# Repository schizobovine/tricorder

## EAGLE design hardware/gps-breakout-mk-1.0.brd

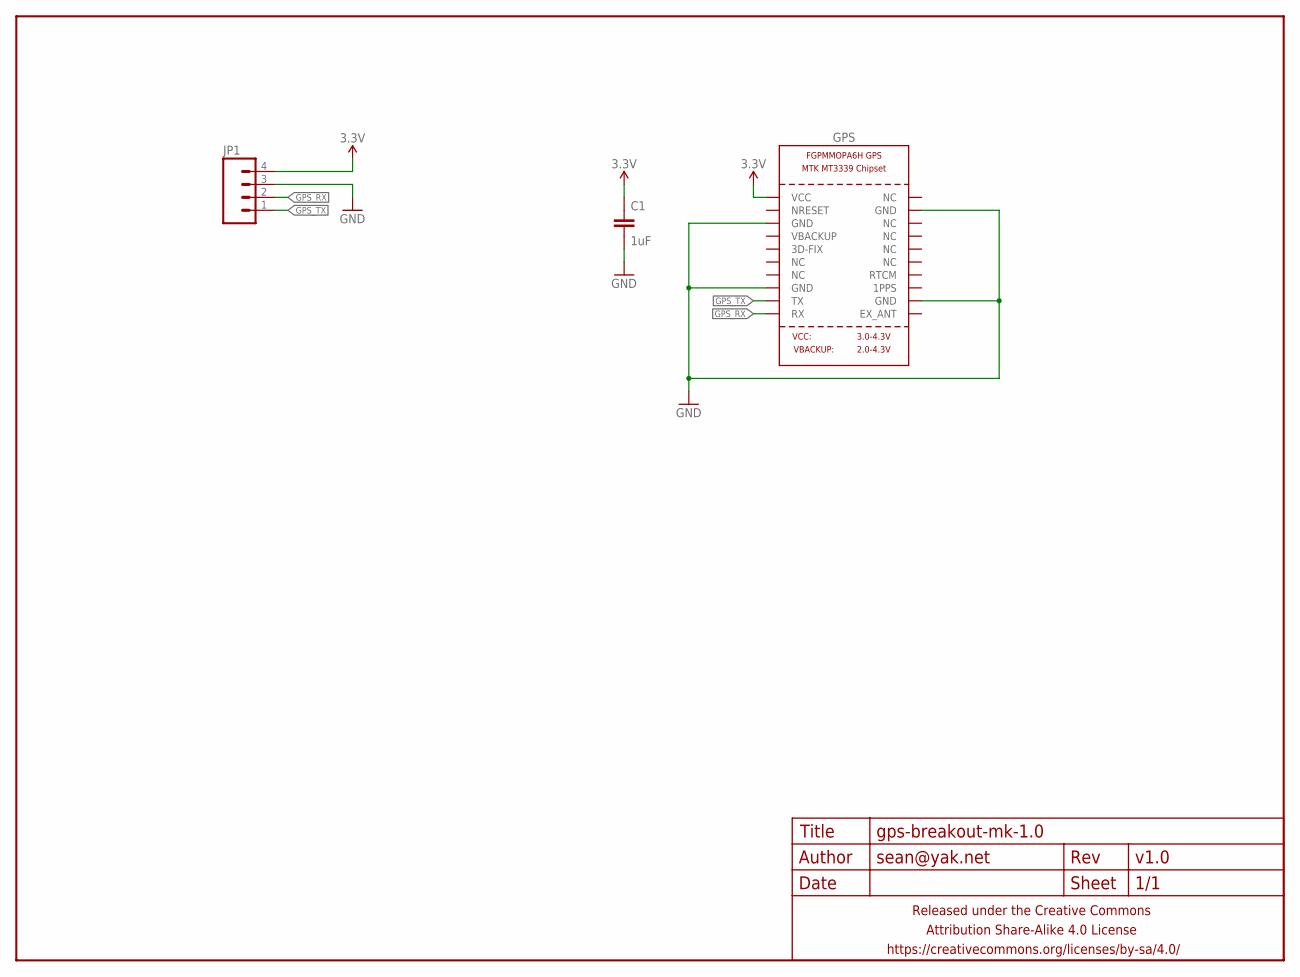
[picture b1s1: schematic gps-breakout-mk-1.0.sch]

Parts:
C1: 1uF; C0603
FRAME1: FRAME-LETTERNO_PACKAGE; DUMMY
GPS: GPS_FGPMMOPA6H; FGPMMOPA6H
JP1: M04PTH-NS-CENTERED; 1X04-PTH-VERT-NS-CENTERED

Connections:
3.3V: C1.1, GPS.P$1 (VCC), JP1.4
GND: C1.2, GPS.P$3 (GND), GPS.P$8 (GND), GPS.P$12 (GND), GPS.P$19 (GND), JP1.3
GPS_RX: GPS.P$10 (RX), JP1.2
GPS_TX: GPS.P$9 (TX), JP1.1

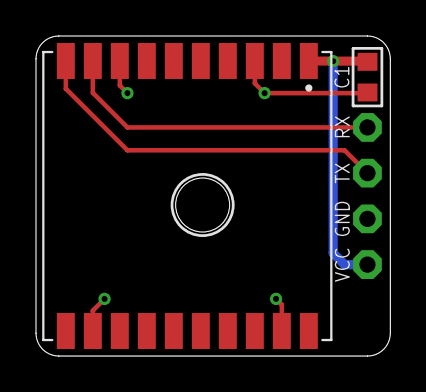
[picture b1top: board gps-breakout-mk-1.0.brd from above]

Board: 2 copper layers, 19.7 x 17.8 mm, 4 parts (0 on the bottom side), 4 nets.

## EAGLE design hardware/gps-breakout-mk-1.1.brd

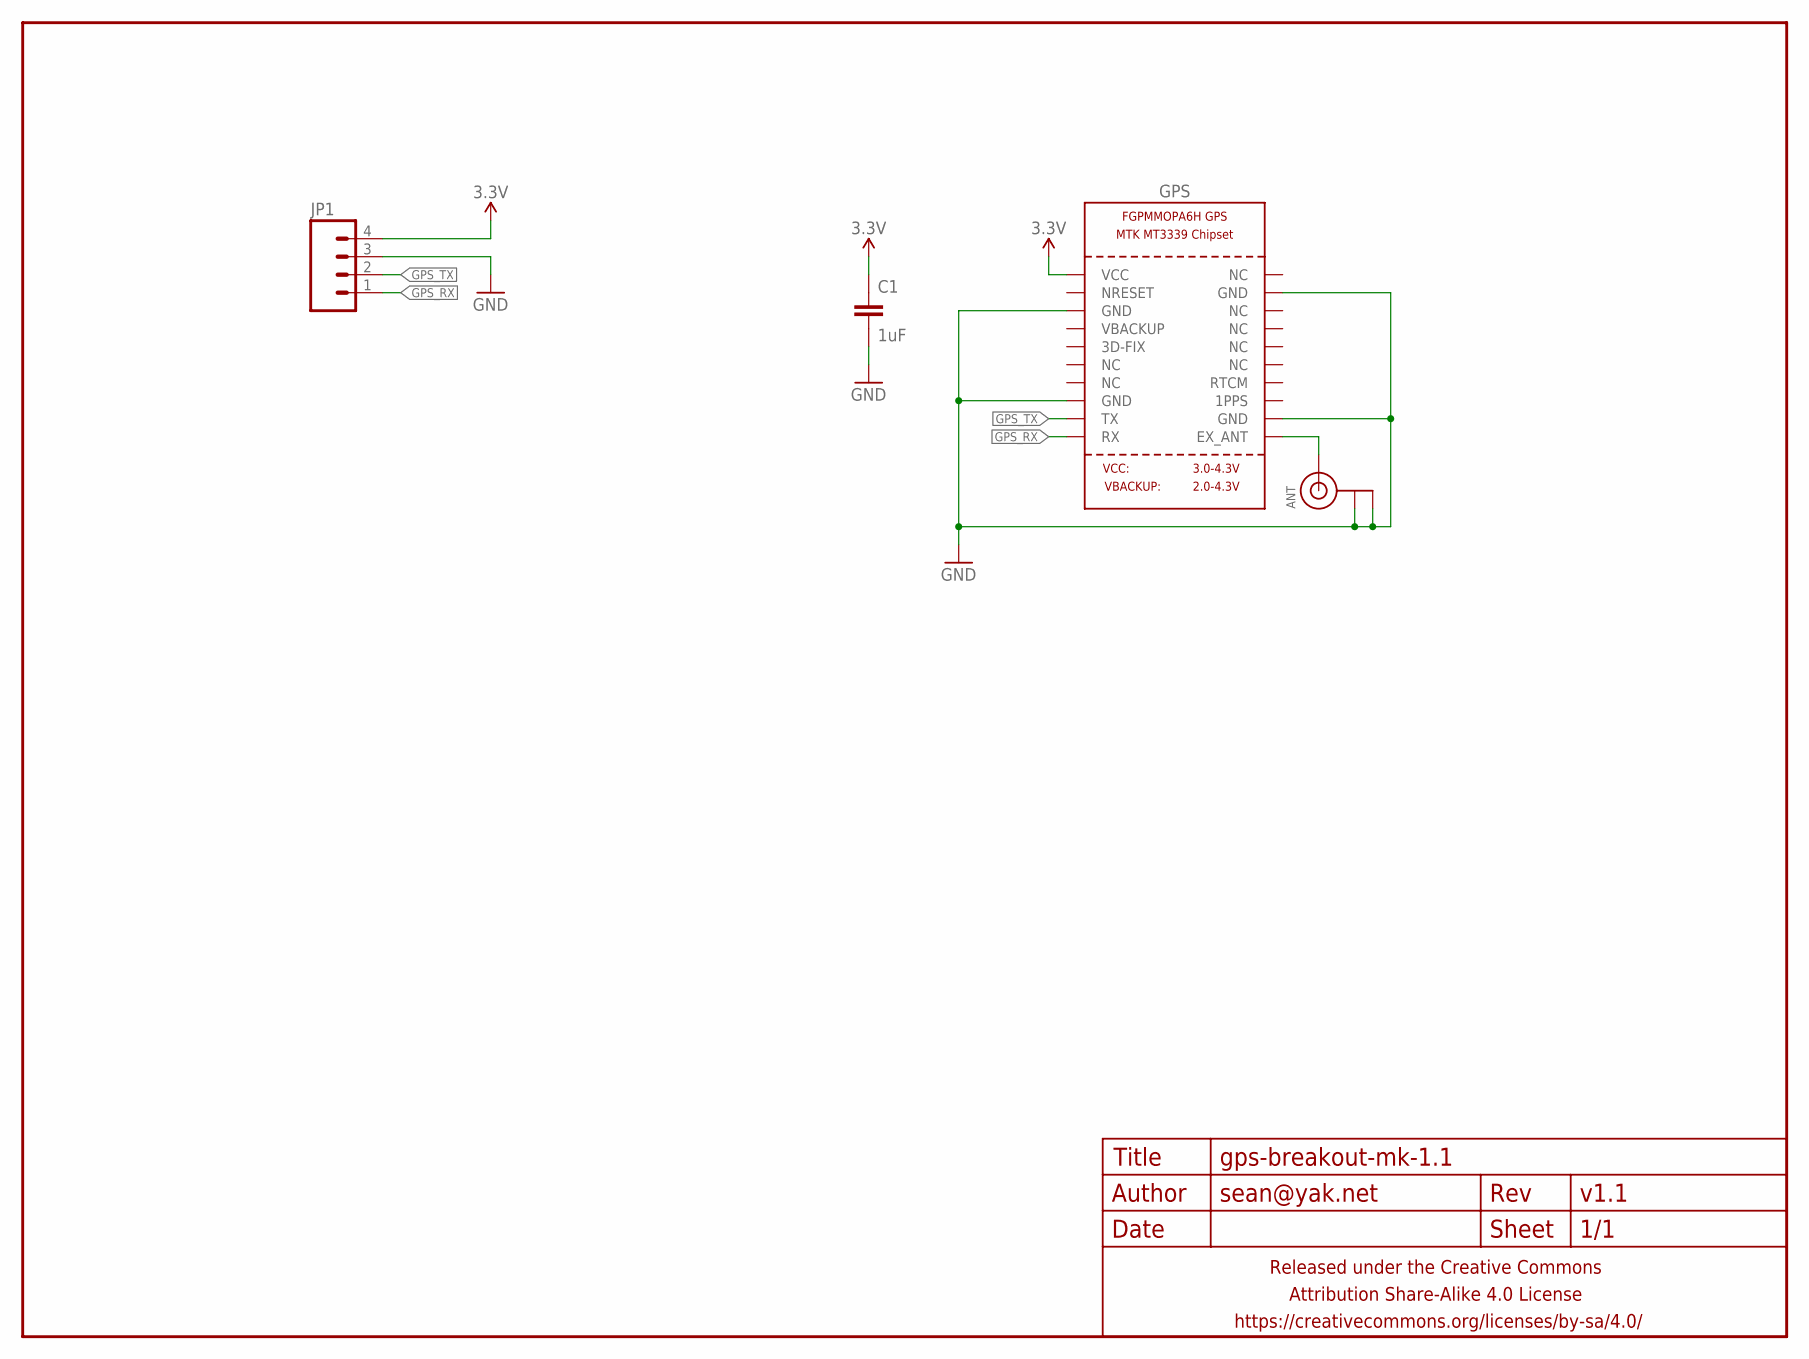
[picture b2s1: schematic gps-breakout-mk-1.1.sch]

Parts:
ANT: ANTENNA_U.FL; U.FL
C1: 1uF; C0402
FRAME1: FRAME-LETTERNO_PACKAGE; DUMMY
GPS: GPS_FGPMMOPA6H; FGPMMOPA6H
JP1: M04PTH-NS-CENTERED; 1X04-PTH-VERT-NS-CENTERED

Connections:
3.3V: C1.1, GPS.P$1 (VCC), JP1.4
GND: ANT.1 (GND), ANT.2 (GND), C1.2, GPS.P$3 (GND), GPS.P$8 (GND), GPS.P$12 (GND), GPS.P$19 (GND), JP1.3
GPS_RX: GPS.P$10 (RX), JP1.1
GPS_TX: GPS.P$9 (TX), JP1.2
unnamed: ANT.3 (SIGNAL), GPS.P$11 (EX_ANT)

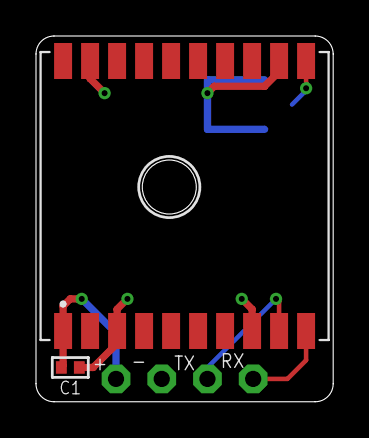
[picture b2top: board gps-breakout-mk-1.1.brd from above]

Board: 2 copper layers, 16.5 x 20.3 mm, 5 parts (1 on the bottom side), 5 nets.

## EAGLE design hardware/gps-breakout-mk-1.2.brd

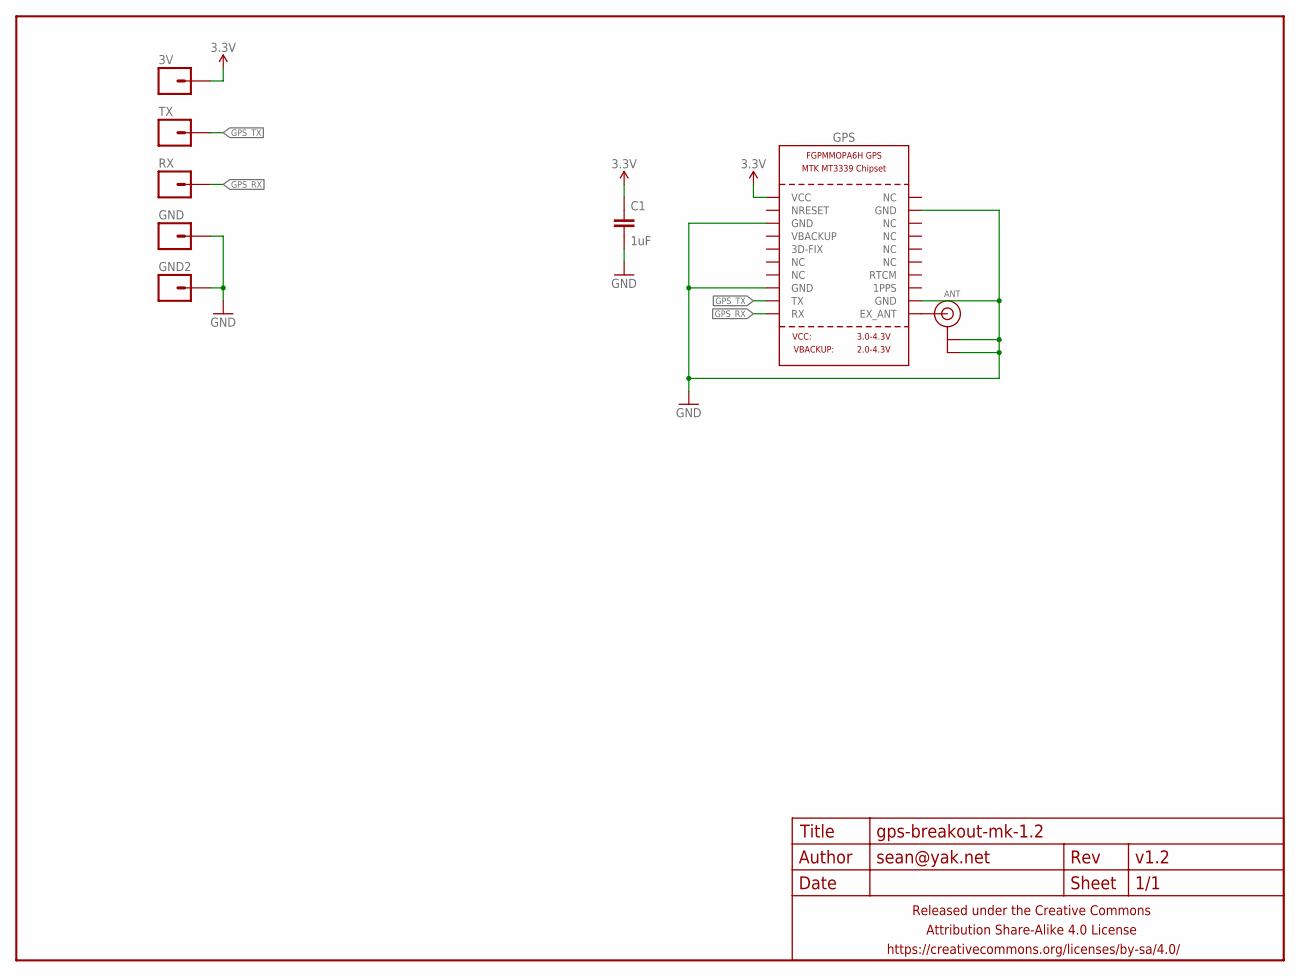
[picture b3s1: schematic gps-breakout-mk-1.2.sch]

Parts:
3V: M01PTH-1MM; 1X01-1MM-NS
ANT: ANTENNA_U.FL; U.FL
C1: 1uF; C0603-TIGHTER
FRAME1: FRAME-LETTERNO_PACKAGE; DUMMY
GND, GND2: M01PTH-1MM; 1X01-1MM-NS
GPS: GPS_FGPMMOPA6H; FGPMMOPA6H
RX: M01PTH-1MM; 1X01-1MM-NS
TX: M01PTH-1MM; 1X01-1MM-NS

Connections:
3.3V: 3V.1, C1.1, GPS.P$1 (VCC)
GND: ANT.1 (GND), ANT.2 (GND), C1.2, GND.1, GND2.1, GPS.P$3 (GND), GPS.P$8 (GND), GPS.P$12 (GND), GPS.P$19 (GND)
GPS_RX: GPS.P$10 (RX), RX.1
GPS_TX: GPS.P$9 (TX), TX.1
unnamed: ANT.3 (SIGNAL), GPS.P$11 (EX_ANT)

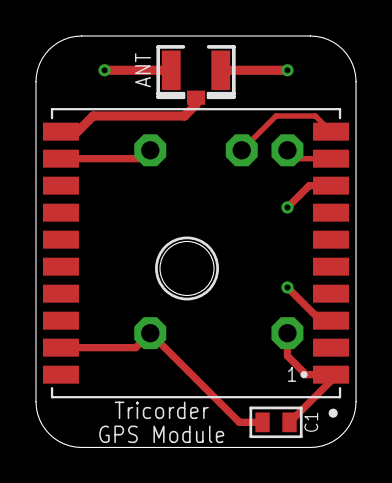
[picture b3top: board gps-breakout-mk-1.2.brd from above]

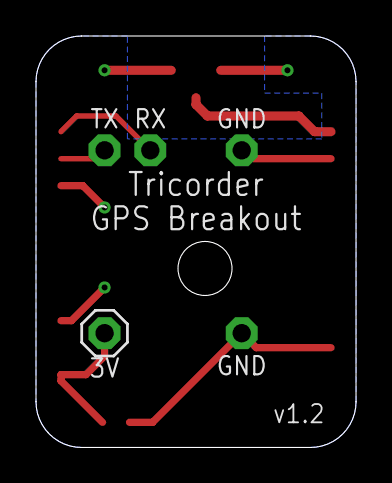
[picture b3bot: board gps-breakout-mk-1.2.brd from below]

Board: 2 copper layers, 17.8 x 22.9 mm, 9 parts (5 on the bottom side), 5 nets.

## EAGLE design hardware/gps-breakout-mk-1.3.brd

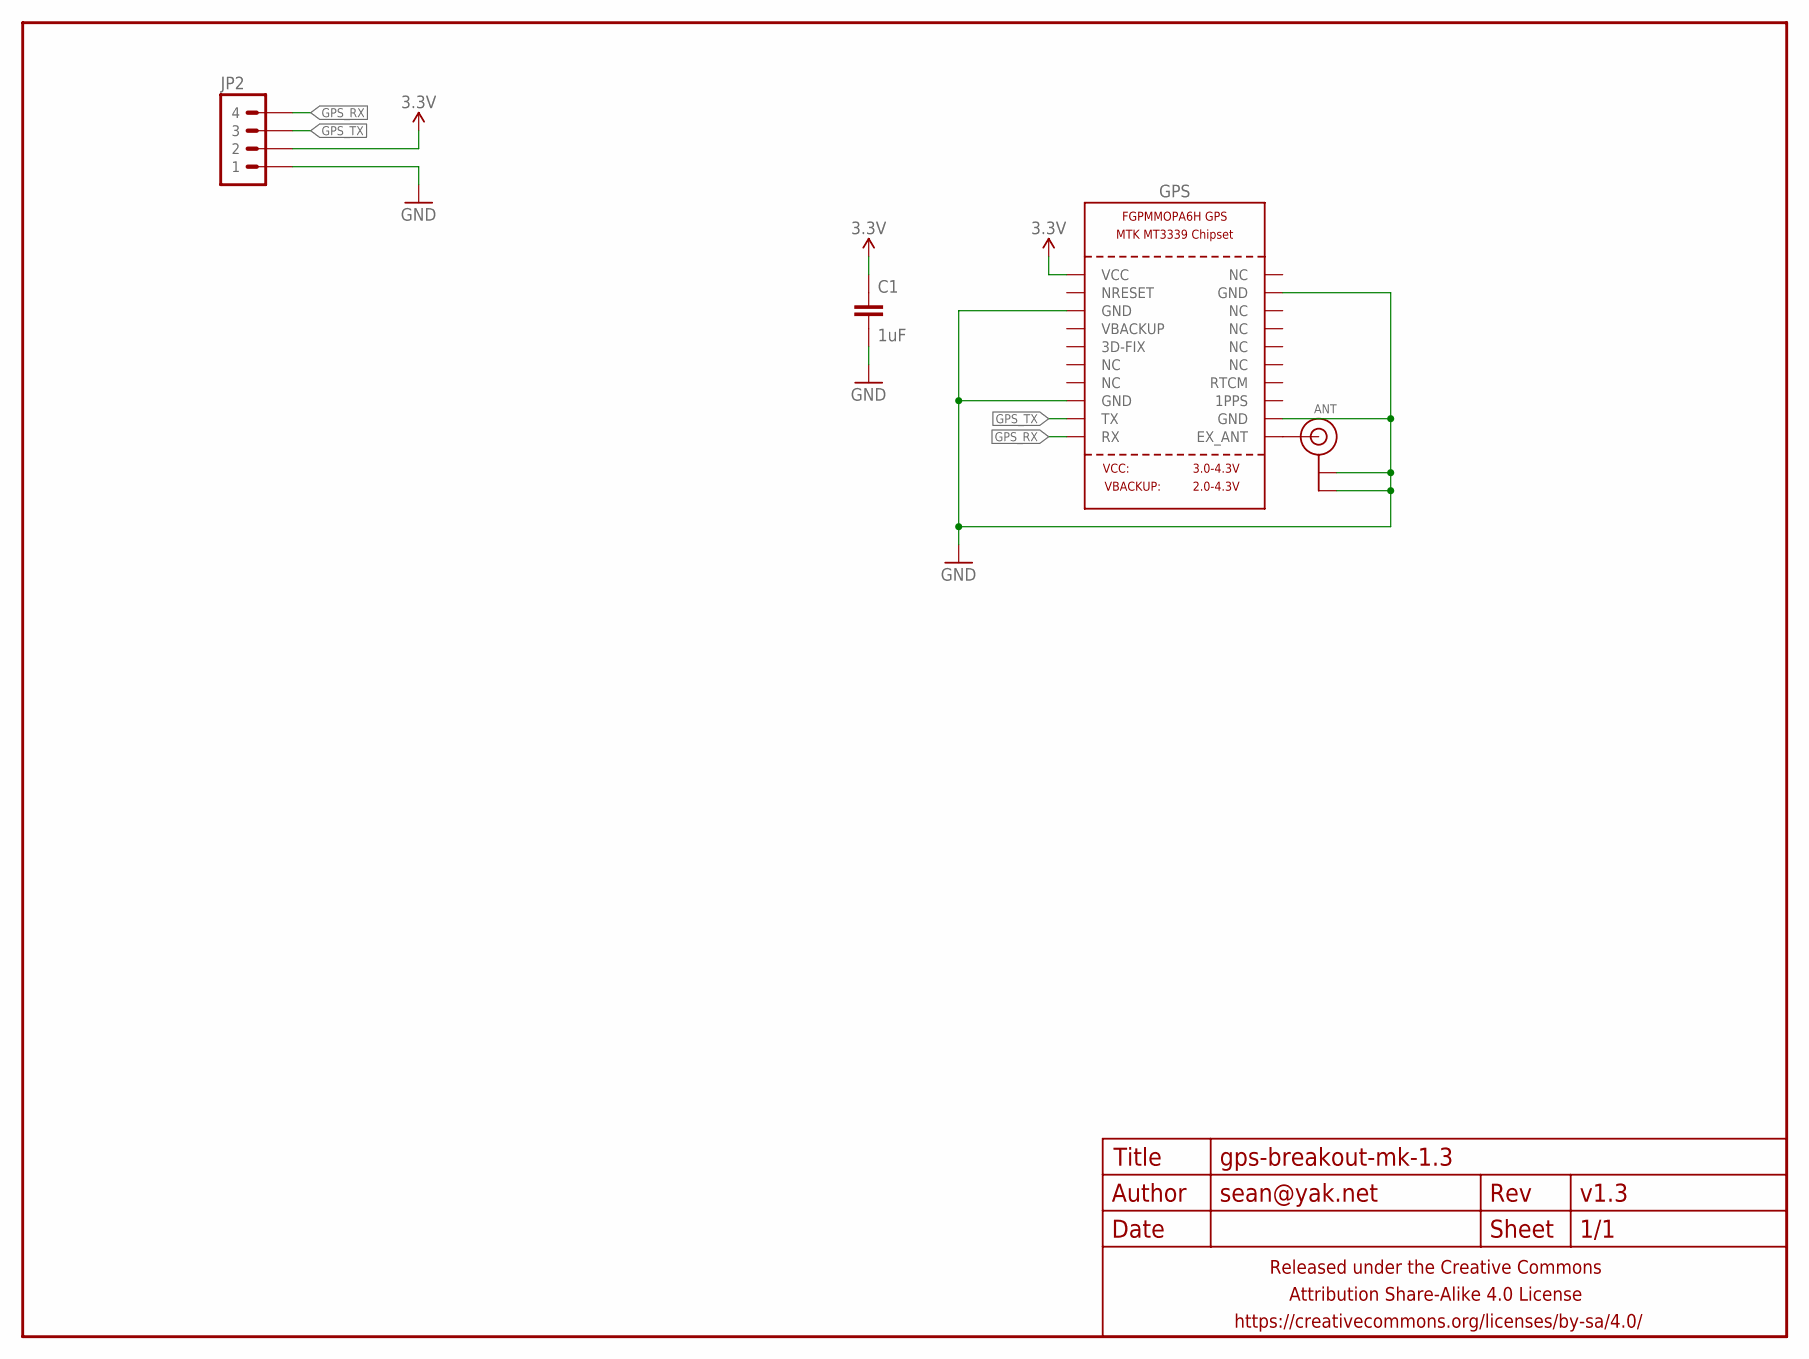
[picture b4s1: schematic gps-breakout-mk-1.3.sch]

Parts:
ANT: ANTENNAUFL; U.FL
C1: 1uF; C0603-TIGHTER
FRAME1: FRAME-LETTERNO_PACKAGE; DUMMY
GPS: GPS_FGPMMOPA6H; FGPMMOPA6H
JP2: M04SMD-FEMALE; 1X04-SMD-FEMALE-RA

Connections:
3.3V: C1.1, GPS.P$1 (VCC), JP2.P$2 (2)
GND: ANT.1 (GND), ANT.2 (GND), C1.2, GPS.P$3 (GND), GPS.P$8 (GND), GPS.P$12 (GND), GPS.P$19 (GND), JP2.P$1 (1)
GPS_RX: GPS.P$10 (RX), JP2.P$4 (4)
GPS_TX: GPS.P$9 (TX), JP2.P$3 (3)
unnamed: ANT.3 (SIGNAL), GPS.P$11 (EX_ANT)

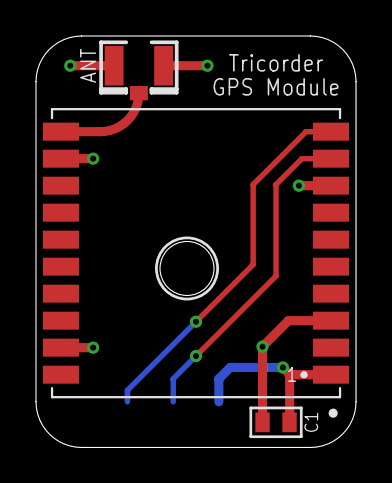
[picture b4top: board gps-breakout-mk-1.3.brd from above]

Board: 2 copper layers, 17.8 x 22.9 mm, 5 parts (1 on the bottom side), 5 nets.

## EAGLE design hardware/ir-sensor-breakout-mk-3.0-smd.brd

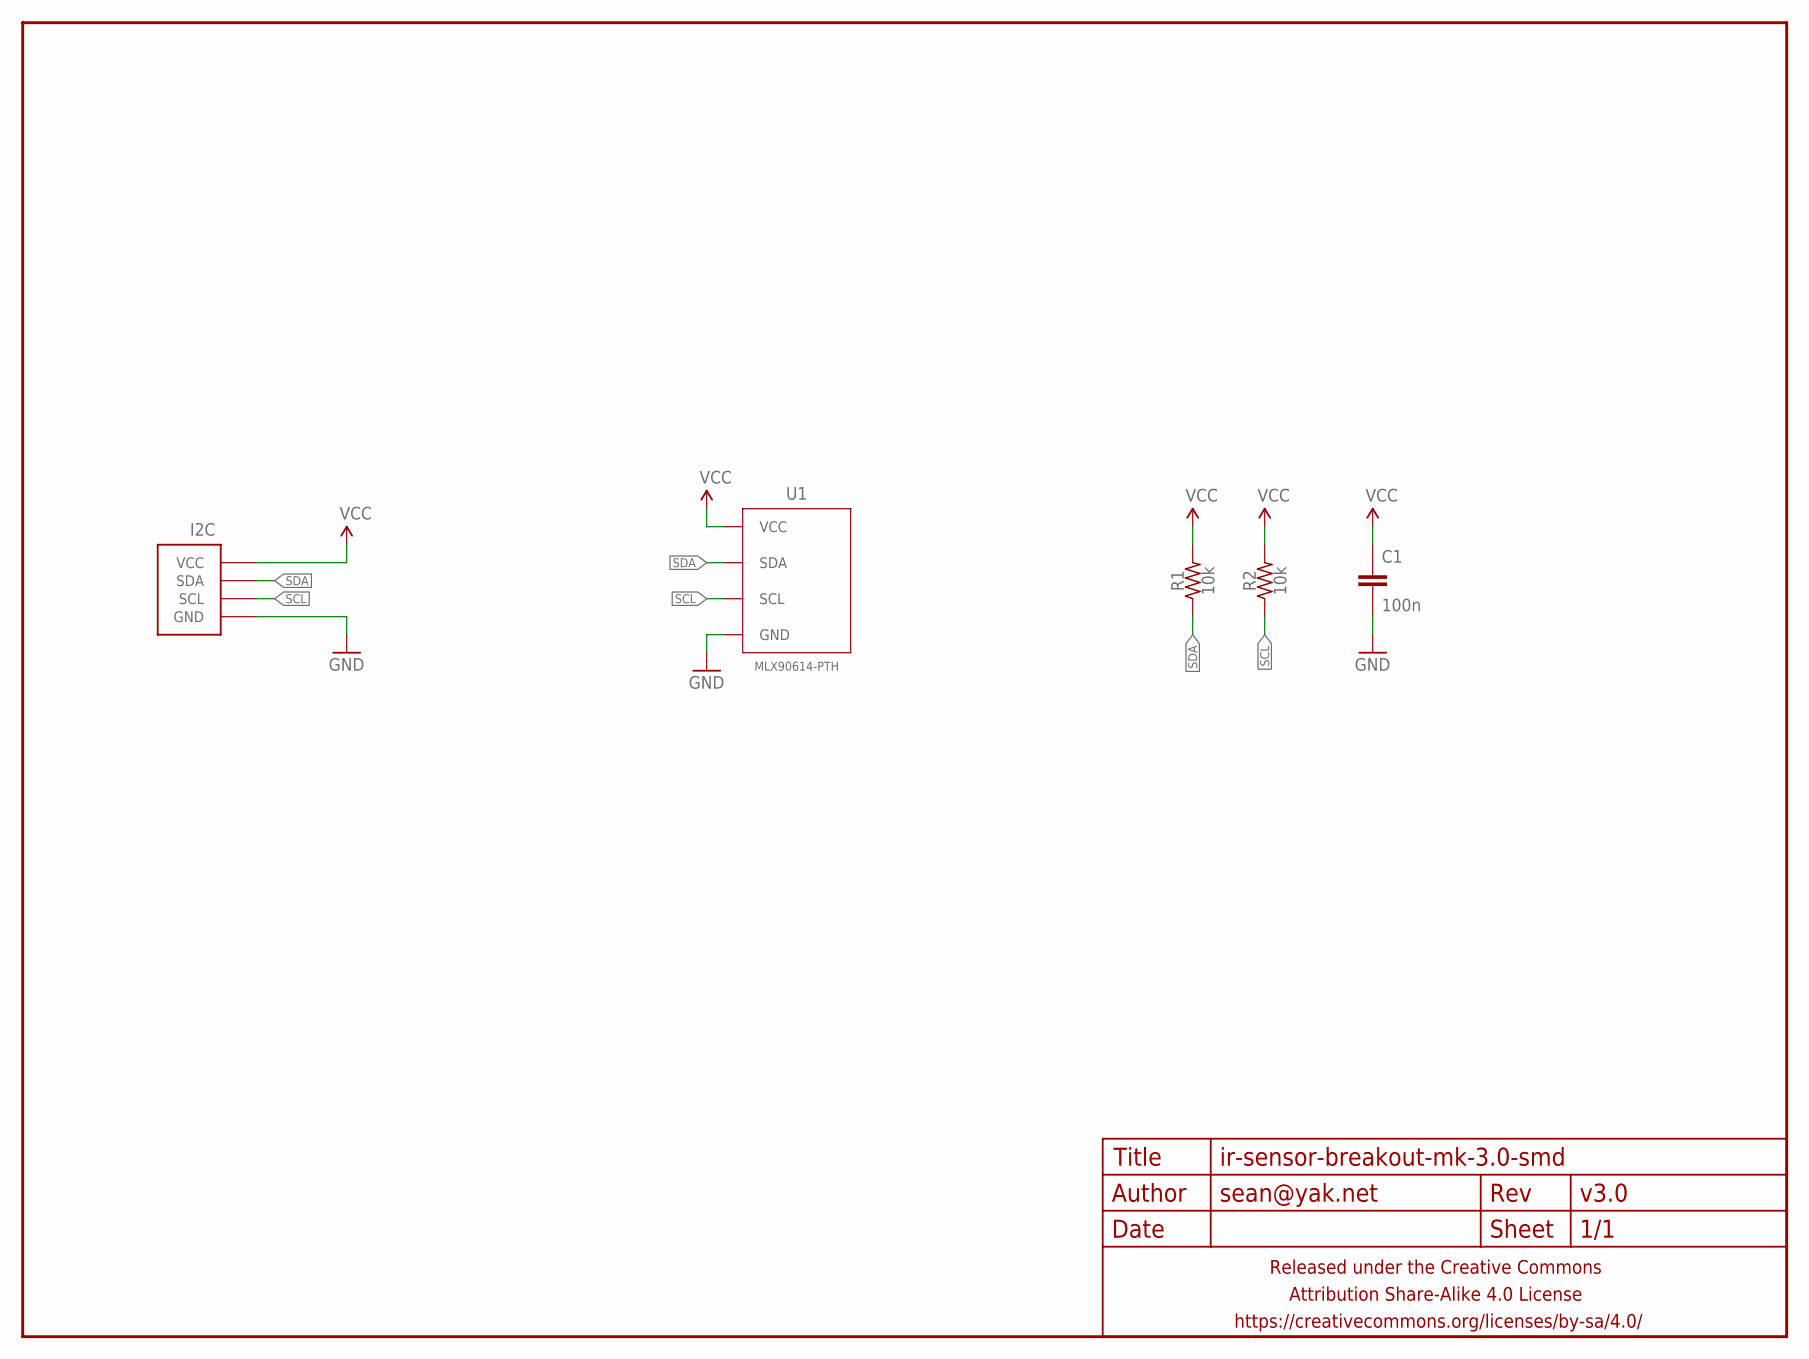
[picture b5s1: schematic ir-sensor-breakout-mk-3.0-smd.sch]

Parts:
C1: 100n; C0805
FRAME1: FRAME-LETTERNO_PACKAGE; DUMMY
I2C: M04-I2CPTH-0.1IN-CENTERED-FLIPPED; 1X04-PTH-VERT-I2C-CENTERED-FLIPPED
R1, R2: 10k; R0805
U1: MLX90614-PTH; TO-39-4

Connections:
GND: C1.2, I2C.GND, U1.4 (GND)
SCL: I2C.SCL, R2.1, U1.1 (SCL)
SDA: I2C.SDA, R1.1, U1.2 (SDA)
VCC: C1.1, I2C.VCC, R1.2, R2.2, U1.3 (VCC)

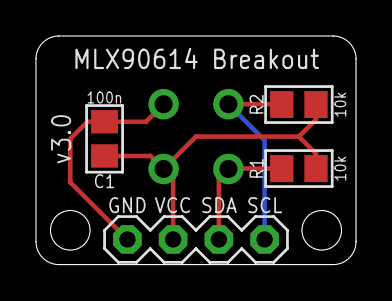
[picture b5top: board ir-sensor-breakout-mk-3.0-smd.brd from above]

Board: 2 copper layers, 17.8 x 12.7 mm, 6 parts (1 on the bottom side), 4 nets.

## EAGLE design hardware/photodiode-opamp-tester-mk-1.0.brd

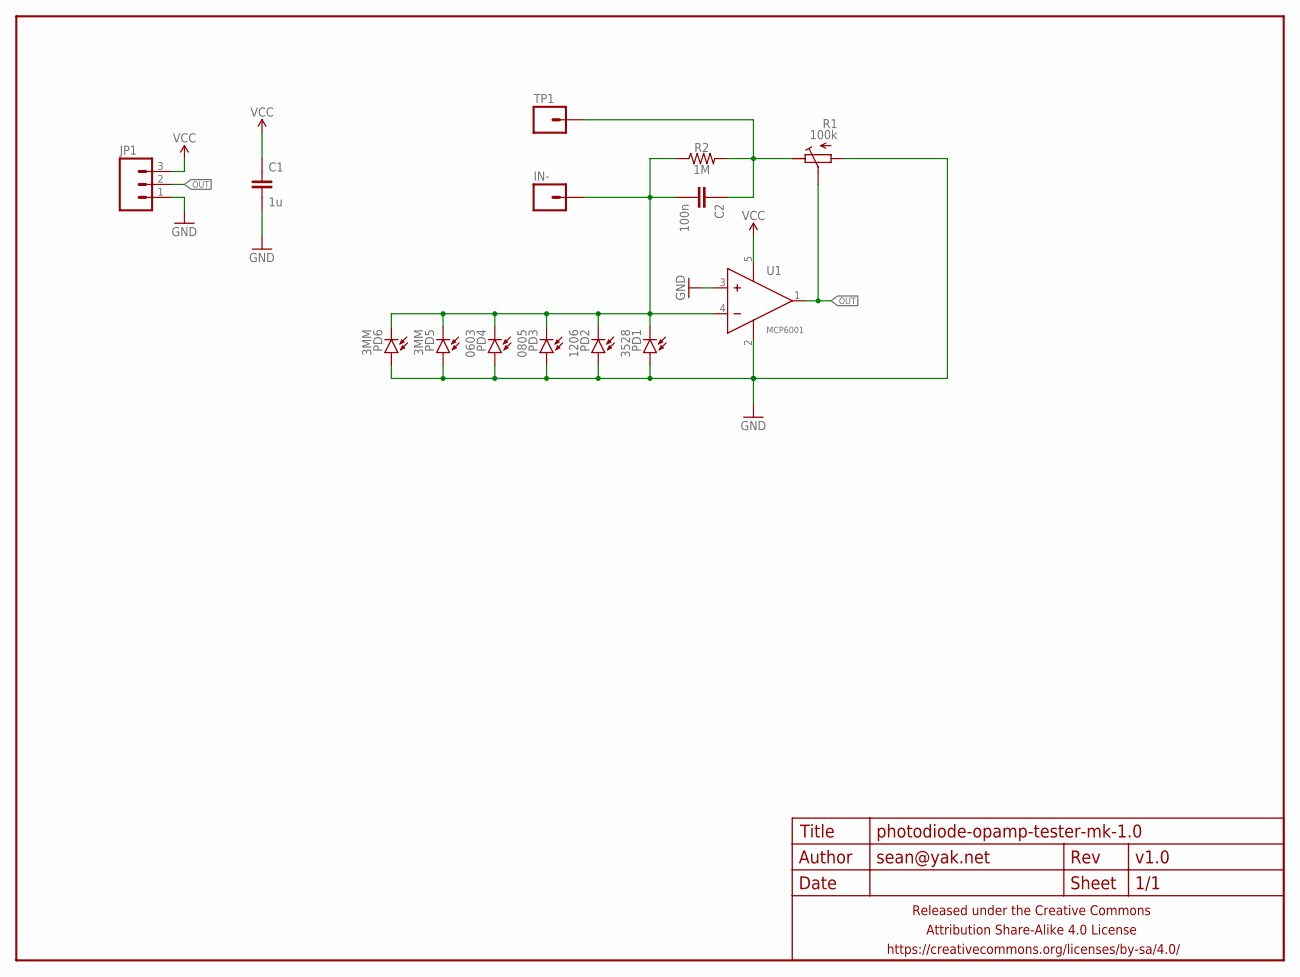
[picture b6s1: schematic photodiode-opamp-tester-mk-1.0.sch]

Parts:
C1: 1u; C0603
C2: 100n; C0603
FRAME1: FRAME-LETTERNO_PACKAGE; DUMMY
IN-: M01PTH; 1X01
JP1: M03PTH-CENTERED; 1X03-CENTERED
PD1: 3528; LED3528
PD2: 1206; LED-1206
PD3: 0805; LED-0805
PD4: 0603; LED-0603
PD5: 3MM; LED3MM-LESSSILK
PD6: 3MM; LED5MM_SHORTPADS
R1: 100k; EVM3Y
R2: 1M; R0603
TP1: M01PTH; 1X01
U1: MCP6001; SOT23-5

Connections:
GND: C1.2, JP1.1, PD1.A, PD2.A, PD3.A, PD4.A, PD5.A, PD6.A, R1.A, U1.2 (V-), U1.3 (IN+)
unnamed: C2.1, R1.E, R2.2, TP1.1
unnamed: C2.2, IN-.1, PD1.K (C), PD2.C, PD3.C, PD4.C, PD5.K (C), PD6.K (C), R2.1, U1.4 (IN-)
OUT: JP1.2, R1.S, U1.1 (OUT)
VCC: C1.1, JP1.3, U1.5 (V+)

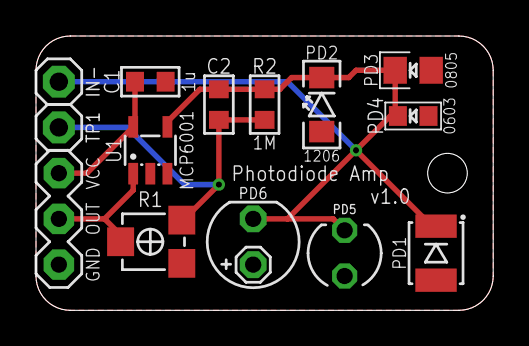
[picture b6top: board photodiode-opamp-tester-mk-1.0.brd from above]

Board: 2 copper layers, 25.4 x 15.2 mm, 15 parts (1 on the bottom side), 5 nets.

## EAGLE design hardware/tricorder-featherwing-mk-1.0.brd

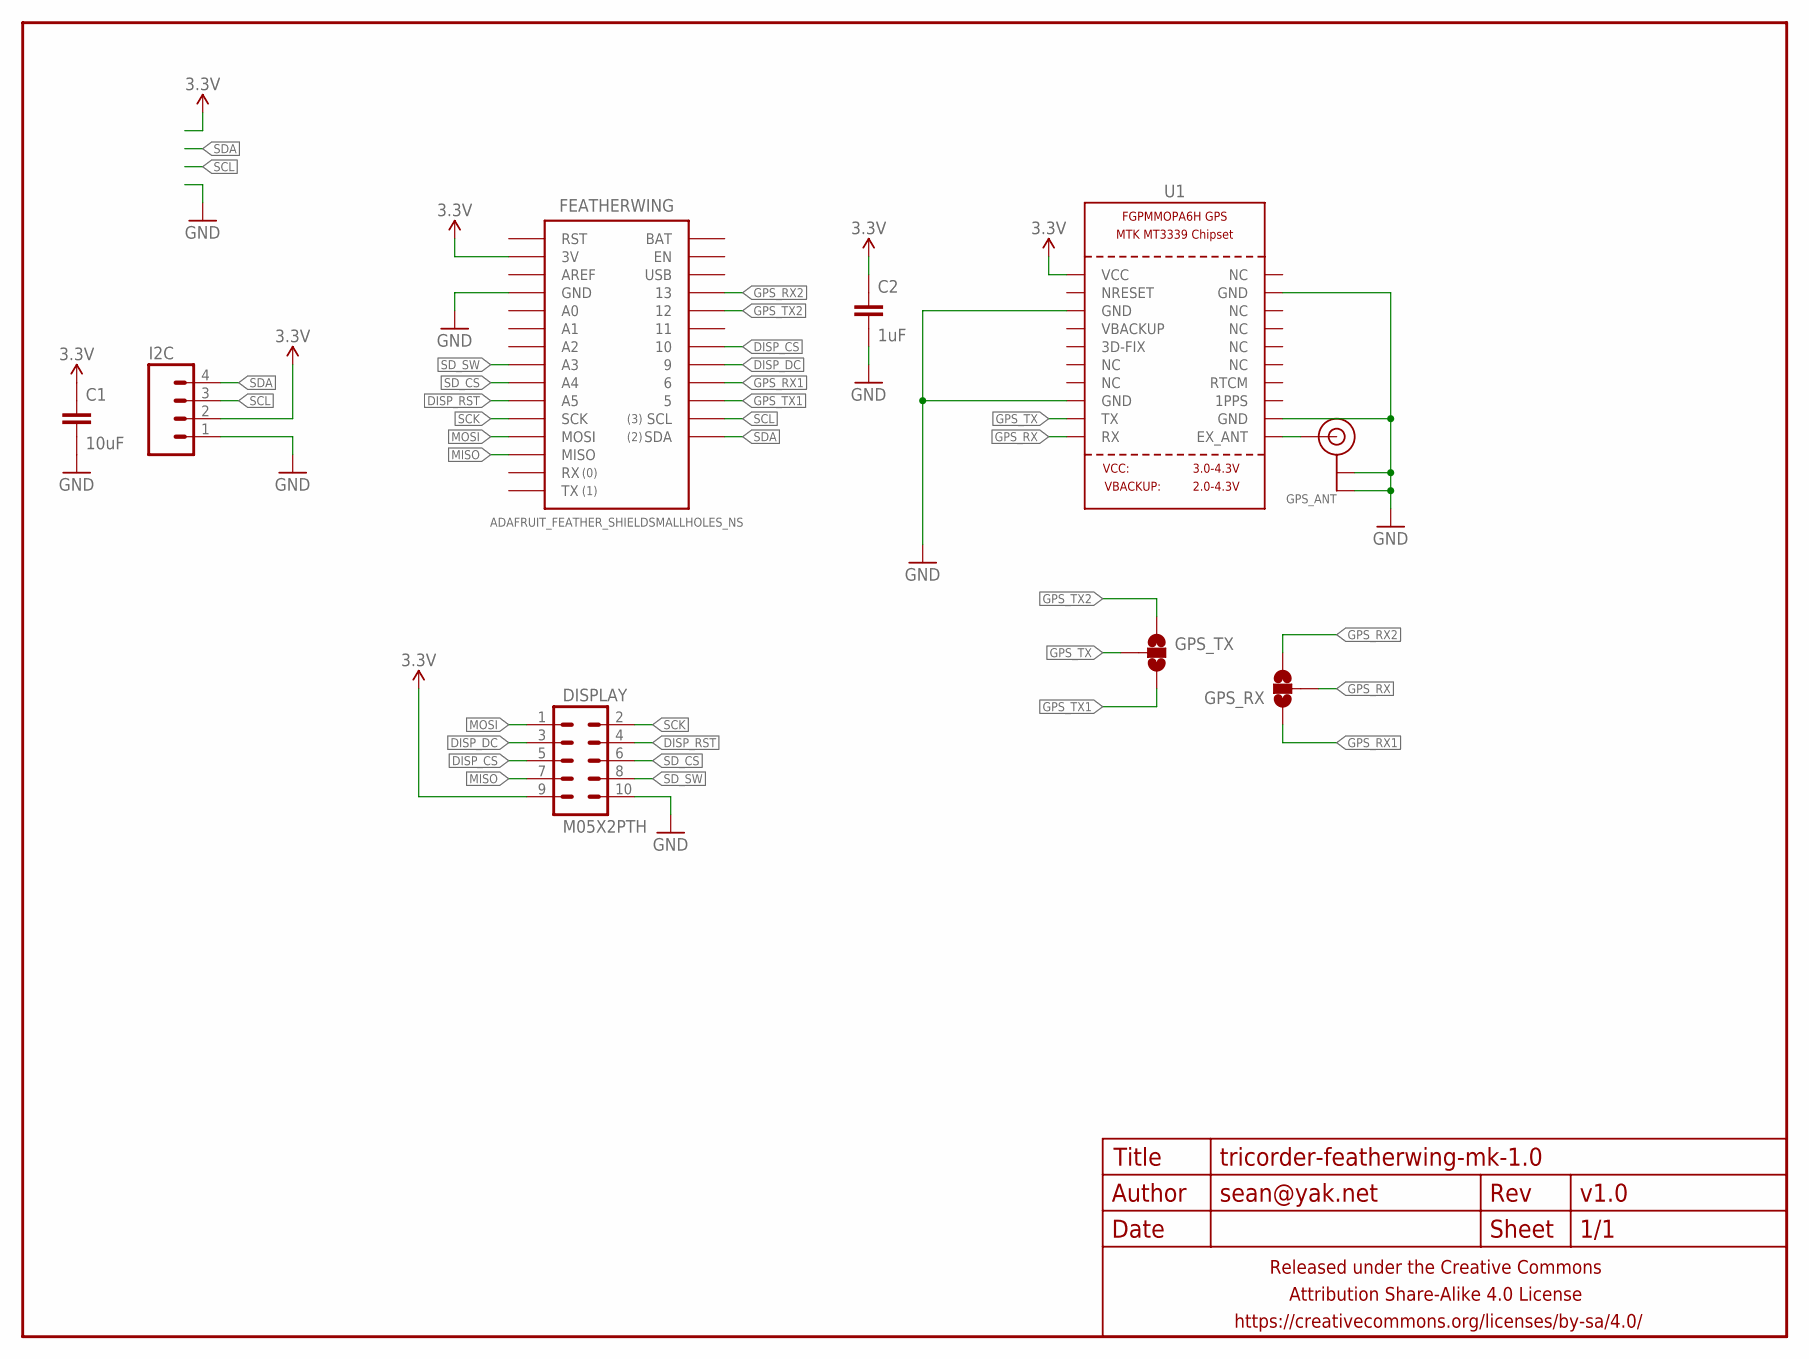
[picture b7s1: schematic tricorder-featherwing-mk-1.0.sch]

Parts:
C1: 10uF; C1210
C2: 1uF; C0603
DISPLAY: M05X2PTH; AVR_ICSP
FEATHERWING: ADAFRUIT_FEATHER_SHIELDSMALLHOLES_NS; ADAFRUIT_FEATHER_SMALLHOLES_NS
FRAME1: FRAME-LETTERNO_PACKAGE; DUMMY
GPS_ANT: ANTENNA_U.FL; U.FL
GPS_RX: JUMPER-PAD-3-NOFULL_BOX_SILK; PAD-JUMPER-3-NO_YES_SILK_FULL_BOX
GPS_TX: JUMPER-PAD-3-NOFULL_BOX_SILK; PAD-JUMPER-3-NO_YES_SILK_FULL_BOX
I2C: M04PTH; 1X04-PTH-VERT
U1: GPS_FGPMMOPA6H; FGPMMOPA6H

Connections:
3.3V: C1.1, C2.1, DISPLAY.9, FEATHERWING.3V, I2C.2, U1.P$1 (VCC)
DISP_CS: DISPLAY.5, FEATHERWING.10
DISP_DC: DISPLAY.3, FEATHERWING.9
DISP_RST: DISPLAY.4, FEATHERWING.A5
GND: C1.2, C2.2, DISPLAY.10, FEATHERWING.GND@0 (GND), FEATHERWING.GND@1 (GND), GPS_ANT.1 (GND), GPS_ANT.2 (GND), I2C.1, U1.P$3 (GND), U1.P$8 (GND), U1.P$12 (GND), U1.P$19 (GND)
GPS_RX: GPS_RX.2, U1.P$10 (RX)
GPS_RX1: FEATHERWING.6, GPS_RX.1
GPS_RX2: FEATHERWING.13, GPS_RX.3
GPS_TX: GPS_TX.2, U1.P$9 (TX)
GPS_TX1: FEATHERWING.5, GPS_TX.3
GPS_TX2: FEATHERWING.12, GPS_TX.1
MISO: DISPLAY.7, FEATHERWING.MISO
MOSI: DISPLAY.1, FEATHERWING.MOSI
unnamed: GPS_ANT.3 (SIGNAL), U1.P$11 (EX_ANT)
SCK: DISPLAY.2, FEATHERWING.SCK
SCL: FEATHERWING.SCL, I2C.3
SDA: FEATHERWING.SDA, I2C.4
SD_CS: DISPLAY.6, FEATHERWING.A4
SD_SW: DISPLAY.8, FEATHERWING.A3

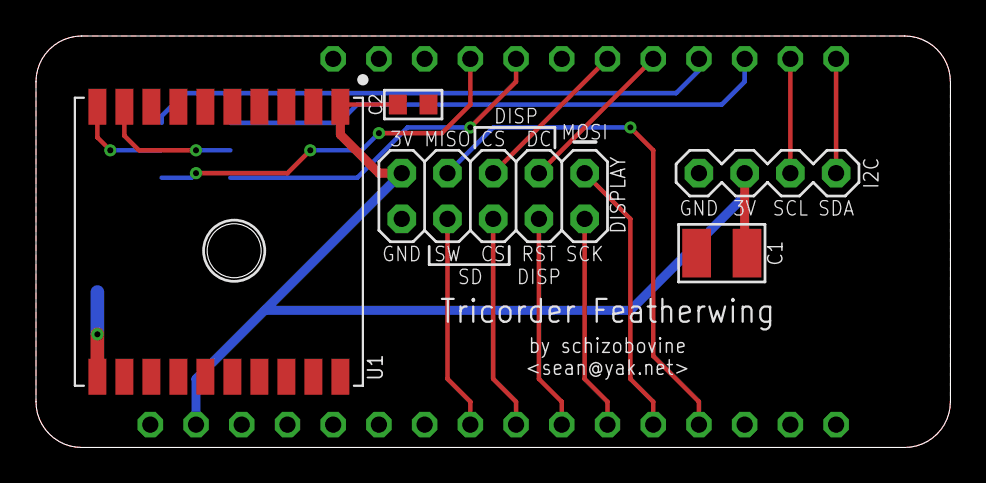
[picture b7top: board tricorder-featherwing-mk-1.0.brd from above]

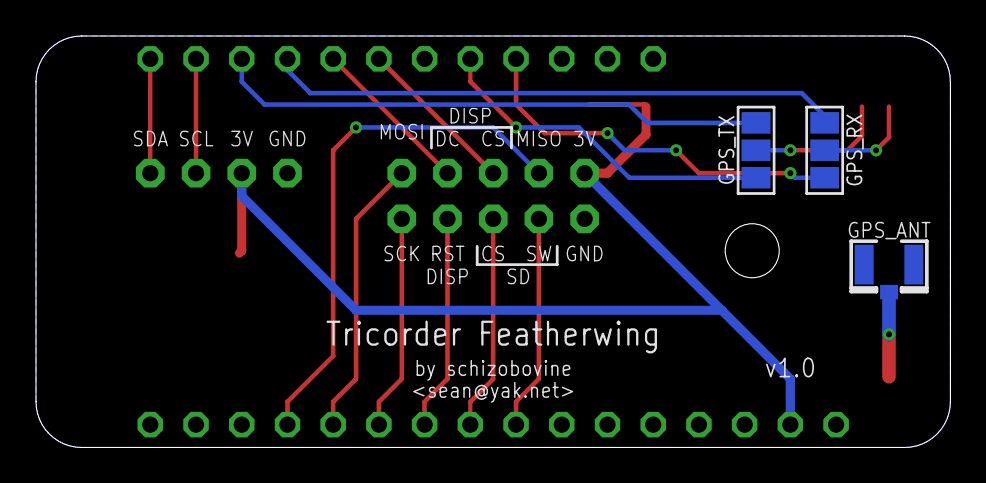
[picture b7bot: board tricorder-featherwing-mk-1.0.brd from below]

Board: 2 copper layers, 50.8 x 22.9 mm, 10 parts (3 on the bottom side), 19 nets.

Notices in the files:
parts and their libraries:
a_parts: Released under the Creative Commons Attribution Share-Alike 4.0 License
a_parts: https://creativecommons.org/licenses/by-sa/4.0
a_parts: Released under the Creative Commons
